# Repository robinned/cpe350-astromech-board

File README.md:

# cpe350-astromech-board
Main control board design for Cal Poly Robotics' astromech, Pascal. Designed by CPE350 Naboo Networks team.

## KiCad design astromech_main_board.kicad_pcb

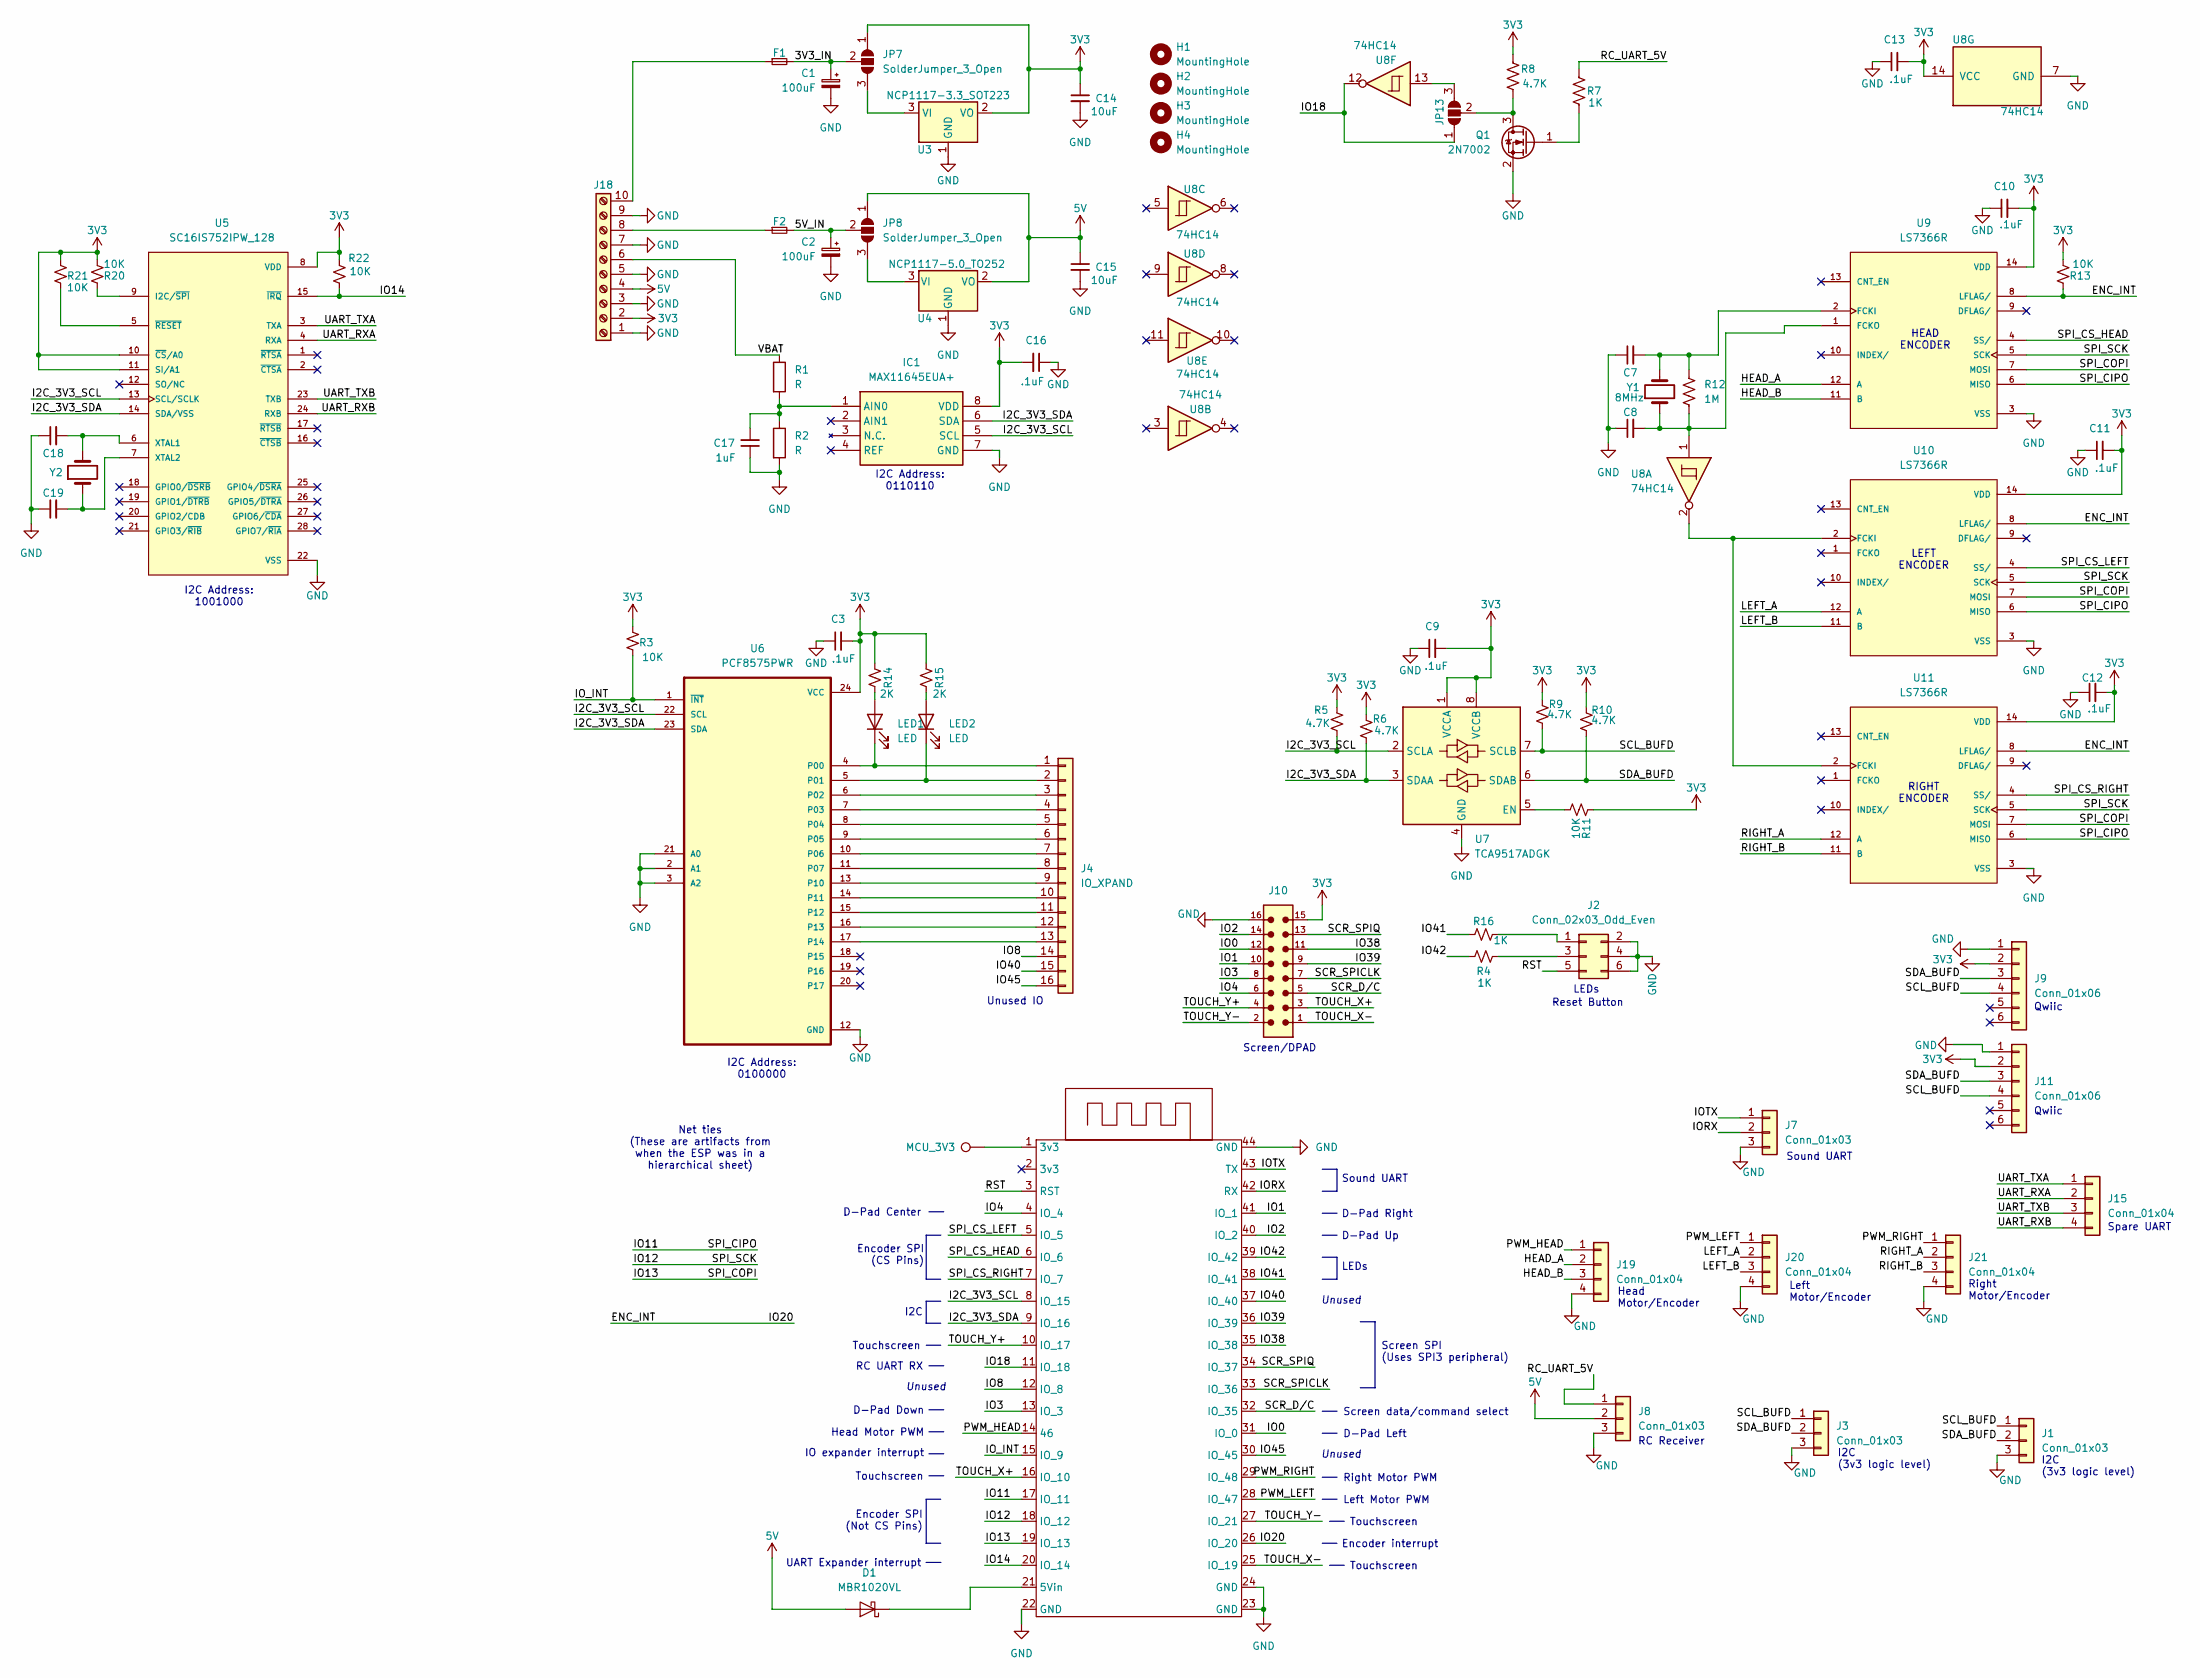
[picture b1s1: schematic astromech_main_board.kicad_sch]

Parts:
C1, C2: 100uF; CP_Elec_6.3x5.8
C3, C9, C10, C11, C12, C13, C16: .1uF; C_1206_3216Metric
C7, C8, C18, C19: C_Small; C_1206_3216Metric
C14, C15: 10uF; C_1206_3216Metric
C17: 1uF; C_1206_3216Metric
D1: MBR1020VL; D_SOD-123F
F1, F2: ??A; Fuseholder_Blade_Mini_Keystone_3568
H1, H2, H3, H4: MountingHole; MountingHole_3.2mm_M3
IC1: MAX11645EUA+; 21-0036K_MXM; Mouser Part Number 700-MAX11645EUA+
J1, J3, J7: Conn_01x03; 691210910003
J2: Conn_02x03_Odd_Even; PinHeader_2x03_P2.54mm_Vertical
J4: IO_XPAND; CUI_TBL009V-254-16GY-2GY
J8: Conn_01x03; PinSocket_1x03_P2.54mm_Vertical
J9, J11: Conn_01x06; CONN_SM04B-SRSS-TB_JST
J10: 61201621621; PART-NUMBER 61201621621
J15, J19, J20, J21: Conn_01x04; 691210910004
J18: Screw_Terminal_01x10; PHOENIX_1984691
JP7, JP8, JP13: SolderJumper_3_Open; SolderJumper-3_P1.3mm_Open_RoundedPad1.0x1.5mm
LED1, LED2: LED; LED_1206_3216Metric_Pad1.42x1.75mm_HandSolder
MCU_3V3: TestPoint; TestPoint_Pad_D1.0mm
Q1: 2N7002; SOT-23
R1, R2: R; R_1206_3216Metric
R3, R11, R13, R20, R21, R22: 10K; R_1206_3216Metric
R4, R7, R16: 1K; R_1206_3216Metric
R5, R6, R8, R9, R10: 4.7K; R_1206_3216Metric
R12: 1M; R_1206_3216Metric
R14, R15: 2K; R_1206_3216Metric
U3: NCP1117-3.3_SOT223; SOT-223-3_TabPin2
U4: NCP1117-5.0_TO252; TO-252-2
U5: SC16IS752IPW_128; SOP65P640X110-28N; PARTREV 9
U6: PCF8575PWR; SOP65P640X120-24N
U7: TCA9517ADGK; VSSOP-8_3x3mm_P0.65mm
U8: 74HC14; SOIC127P600X175-14N
U9, U10, U11: LS7366R; SOIC14_LS7366R_LSI; PARTREV June 2014
U13: YD-ESP32-S3
Y1: 8MHz; Crystal_SMD_Abracon_ABM3-2Pin_5.0x3.2mm
Y2: Crystal; Crystal_HC49-U_Vertical

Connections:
3V3: C3.2, C9.2, C10.2, C11.2, C12.2, C13.2, C14.1, C16.2, IC1.8 (VDD), J9.2, J10.15, J11.2, J18.2, JP7.1 (A), R3.1, R5.1, R6.1, R8.1, R9.1, R10.1, R11.1, R13.1, R14.1, R15.1, R20.1, R21.1, R22.2, U3.2 (VO), U5.8 (VDD), U5.10 (~CS/A0), U5.11 (SI/A1), U6.24 (VCC), U7.1 (VCCA), U7.8 (VCCB), U8.14 (VCC), U9.14 (VDD), U10.14 (VDD), U11.14 (VDD)
5V: C15.1, D1.2 (A), J8.2, J18.4, JP8.1 (A), U4.2 (VO)
/3V3_IN: C1.1, F1.2, JP7.2 (C)
/5V_IN: C2.1, F2.2, JP8.2 (C)
/ENC_INT: R13.2, U9.8 (LFLAG/), U10.8 (LFLAG/), U11.8 (LFLAG/), U13.26 (IO_20)
/HEAD_A: J19.2, U9.12 (A)
/HEAD_B: J19.3, U9.11 (B)
/I2C_3V3_SCL: IC1.5 (SCL), R5.2, U5.13 (SCL/SCLK), U6.22 (SCL), U7.2 (SCLA), U13.8 (IO_15)
/I2C_3V3_SDA: IC1.6 (SDA), R6.2, U5.14 (SDA/VSS), U6.23 (SDA), U7.3 (SDAA), U13.9 (IO_16)
/IO0: J10.12, U13.31 (IO_0)
/IO1: J10.10, U13.41 (IO_1)
/IO2: J10.14, U13.40 (IO_2)
/IO3: J10.8, U13.13 (IO_3)
/IO4: J10.6, U13.4 (IO_4)
/IO8: J4.14, U13.12 (IO_8)
/IO11: U9.6 (MISO), U10.6 (MISO), U11.6 (MISO), U13.17 (IO_11)
/IO12: U9.5 (SCK), U10.5 (SCK), U11.5 (SCK), U13.18 (IO_12)
/IO13: U9.7 (MOSI), U10.7 (MOSI), U11.7 (MOSI), U13.19 (IO_13)
/IO14: R22.1, U5.15 (~IRQ), U13.20 (IO_14)
/IO18: JP13.1 (A), U8.12, U13.11 (IO_18)
/IO38: J10.11, U13.35 (IO_38)
/IO39: J10.9, U13.36 (IO_39)
/IO40: J4.15, U13.37 (IO_40)
/IO41: R16.1, U13.38 (IO_41)
/IO42: R4.1, U13.39 (IO_42)
/IO45: J4.16, U13.30 (IO_45)
/IORX: J7.2, U13.42 (RX)
/IOTX: J7.1, U13.43 (TX)
/IO_INT: R3.2, U6.1 (~INT), U13.15 (IO_9)
/LEFT_A: J20.2, U10.12 (A)
/LEFT_B: J20.3, U10.11 (B)
/PWM_HEAD: J19.1, U13.14 (46)
/PWM_LEFT: J20.1, U13.28 (IO_47)
/PWM_RIGHT: J21.1, U13.29 (IO_48)
/RC_UART_5V: J8.1, R7.1
/RIGHT_A: J21.2, U11.12 (A)
/RIGHT_B: J21.3, U11.11 (B)
/RST: J2.5, U13.3 (RST)
/SCL_BUFD: J1.1, J3.1, J9.4, J11.4, R9.2, U7.7 (SCLB)
/SCR_D/C: J10.5, U13.32 (IO_35)
/SCR_SPICLK: J10.7, U13.33 (IO_36)
/SCR_SPIQ: J10.13, U13.34 (IO_37)
/SDA_BUFD: J1.2, J3.2, J9.3, J11.3, R10.2, U7.6 (SDAB)
/SPI_CS_HEAD: U9.4 (SS/), U13.6 (IO_6)
/SPI_CS_LEFT: U10.4 (SS/), U13.5 (IO_5)
/SPI_CS_RIGHT: U11.4 (SS/), U13.7 (IO_7)
/TOUCH_X+: J10.3, U13.16 (IO_10)
/TOUCH_X-: J10.1, U13.25 (IO_19)
/TOUCH_Y+: J10.4, U13.10 (IO_17)
/TOUCH_Y-: J10.2, U13.27 (IO_21)
/UART_RXA: J15.2, U5.4 (RXA)
/UART_RXB: J15.4, U5.24 (RXB)
/UART_TXA: J15.1, U5.3 (TXA)
/UART_TXB: J15.3, U5.23 (TXB)
/VBAT: J18.6, R1.1
GND: C1.2, C2.2, C3.1, C7.1, C8.1, C9.1, C10.1, C11.1, C12.1, C13.1, C14.2, C15.2, C16.1, C17.1, C18.1, C19.1, IC1.7 (GND), J1.3, J2.2, J2.4, J2.6, J3.3, J7.3, J8.3, J9.1, J10.16, J11.1, J18.1, J18.3, J18.5, J18.7, J18.9, J19.4, J20.4, J21.4, Q1.2 (S), R2.2, U3.1 (GND), U4.1 (GND), U5.22 (VSS), U6.2 (A1), U6.3 (A2), U6.12 (GND), U6.21 (A0), U7.4 (GND), U8.7 (GND), U9.3 (VSS), U10.3 (VSS), U11.3 (VSS), U13.22 (GND), U13.23 (GND), U13.24 (GND), U13.44 (GND)
unnamed: D1.1 (K), U13.21 (5Vin)
unnamed: C17.2, IC1.1 (AIN0), R1.2, R2.1
unnamed: J2.1, R16.2
unnamed: J2.3, R4.2
unnamed: J4.1, LED1.1 (K), U6.4 (P00)
unnamed: J4.2, LED2.1 (K), U6.5 (P01)
unnamed: J4.3, U6.6 (P02)
unnamed: J4.4, U6.7 (P03)
unnamed: J4.5, U6.8 (P04)
unnamed: J4.6, U6.9 (P05)
unnamed: J4.7, U6.10 (P06)
unnamed: J4.8, U6.11 (P07)
unnamed: J4.9, U6.13 (P10)
unnamed: J4.10, U6.14 (P11)
unnamed: J4.11, U6.15 (P12)
unnamed: J4.12, U6.16 (P13)
unnamed: J4.13, U6.17 (P14)
unnamed: F2.1, J18.8
unnamed: F1.1, J18.10
unnamed: JP7.3 (B), U3.3 (VI)
unnamed: JP8.3 (B), U4.3 (VI)
unnamed: JP13.3 (B), U8.13
unnamed: JP13.2 (C), Q1.3 (D), R8.2
unnamed: LED1.2 (A), R14.2
unnamed: LED2.2 (A), R15.2
unnamed: MCU_3V3.1, U13.1 (3v3)
unnamed: Q1.1 (G), R7.2
unnamed: R20.2, U5.9 (I2C/~SPI)
unnamed: C18.2, U5.6 (XTAL1), Y2.2
unnamed: C19.2, U5.7 (XTAL2), Y2.1
unnamed: R21.2, U5.5 (~RESET)
unnamed: R11.2, U7.5 (EN)
unnamed: C7.2, R12.1, U9.2 (FCKI), Y1.2
unnamed: C8.2, R12.2, U8.1, U9.1 (FCKO), Y1.1
unnamed: U8.2, U10.2 (FCKI), U11.2 (FCKI)

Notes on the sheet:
Head Motor PWM
D-Pad Right
Reset Button
Net ties (These are artifacts from when the ESP was in a hierarchical sheet)
D-Pad Left
Screen SPI (Uses SPI3 peripheral)
I2C
Qwiic
RC UART RX
UART Expander interrupt
Right Motor/Encoder
Touchscreen
Unused IO
Encoder SPI (Not CS Pins)
Encoder interrupt
Encoder SPI (CS Pins)
RIGHT ENCODER
Right Motor PWM
I2C (3v3 logic level)
LEDs
IO expander interrupt
I2C Address: 0110110
Sound UART
LEFT ENCODER
D-Pad Center
Unused
D-Pad Down
HEAD ENCODER
Left Motor PWM
Screen/DPAD
Spare UART
Screen data/command select
Head Motor/Encoder
D-Pad Up
Left Motor/Encoder
I2C Address: 1001000
I2C Address: 0100000
RC Receiver

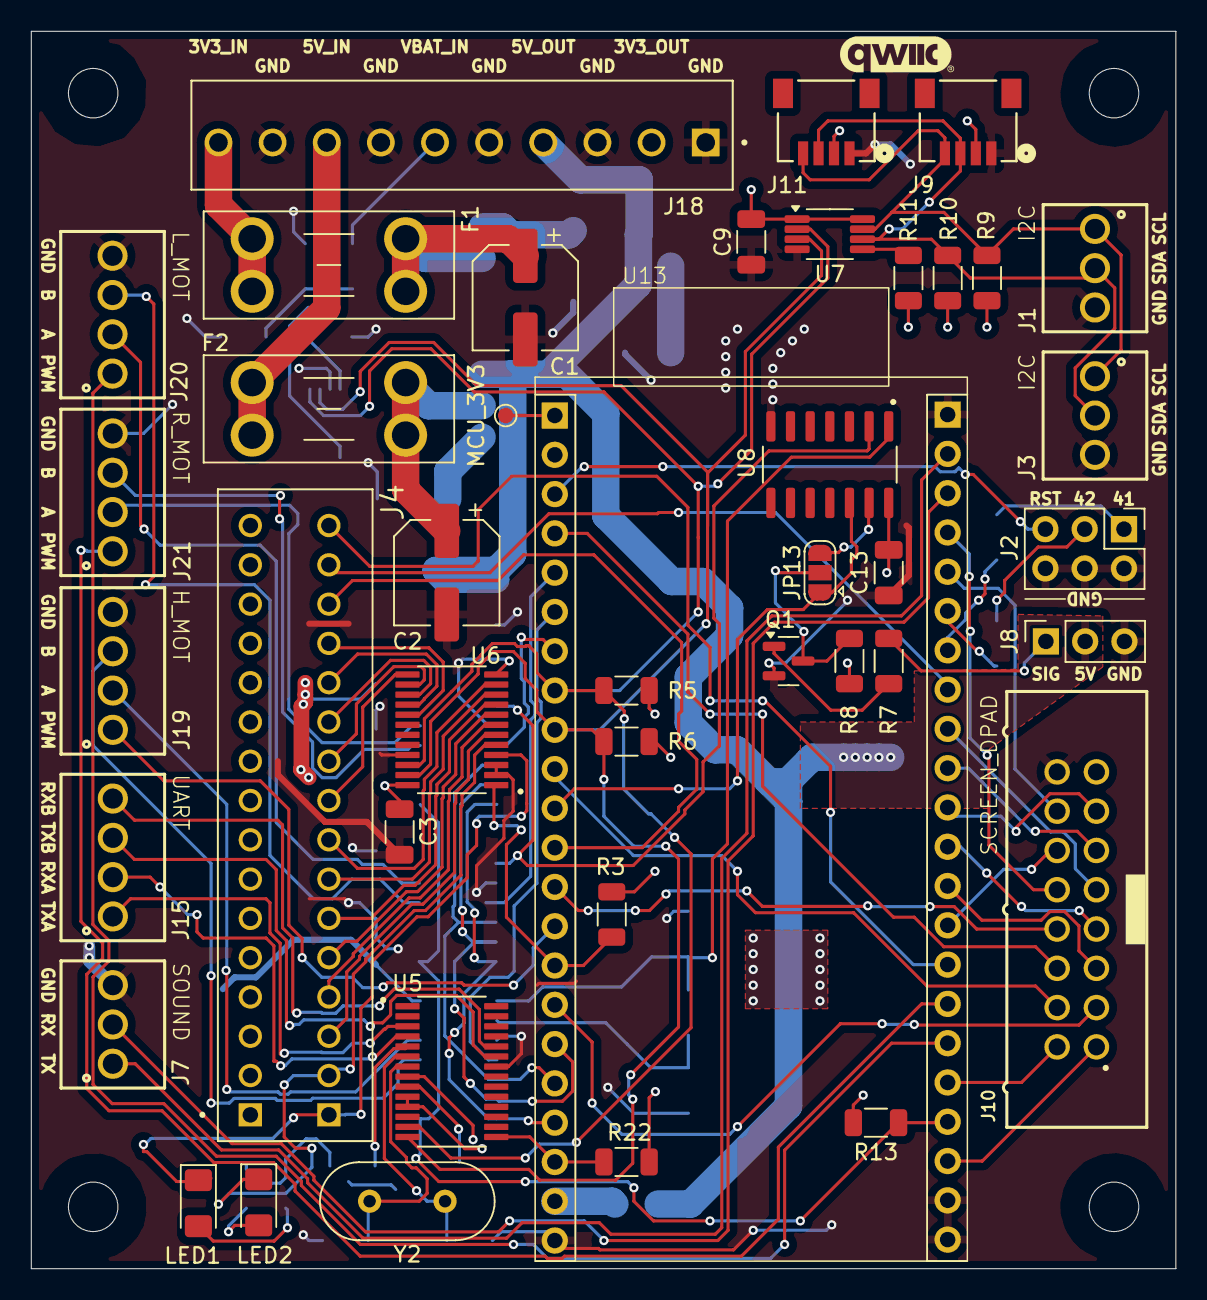
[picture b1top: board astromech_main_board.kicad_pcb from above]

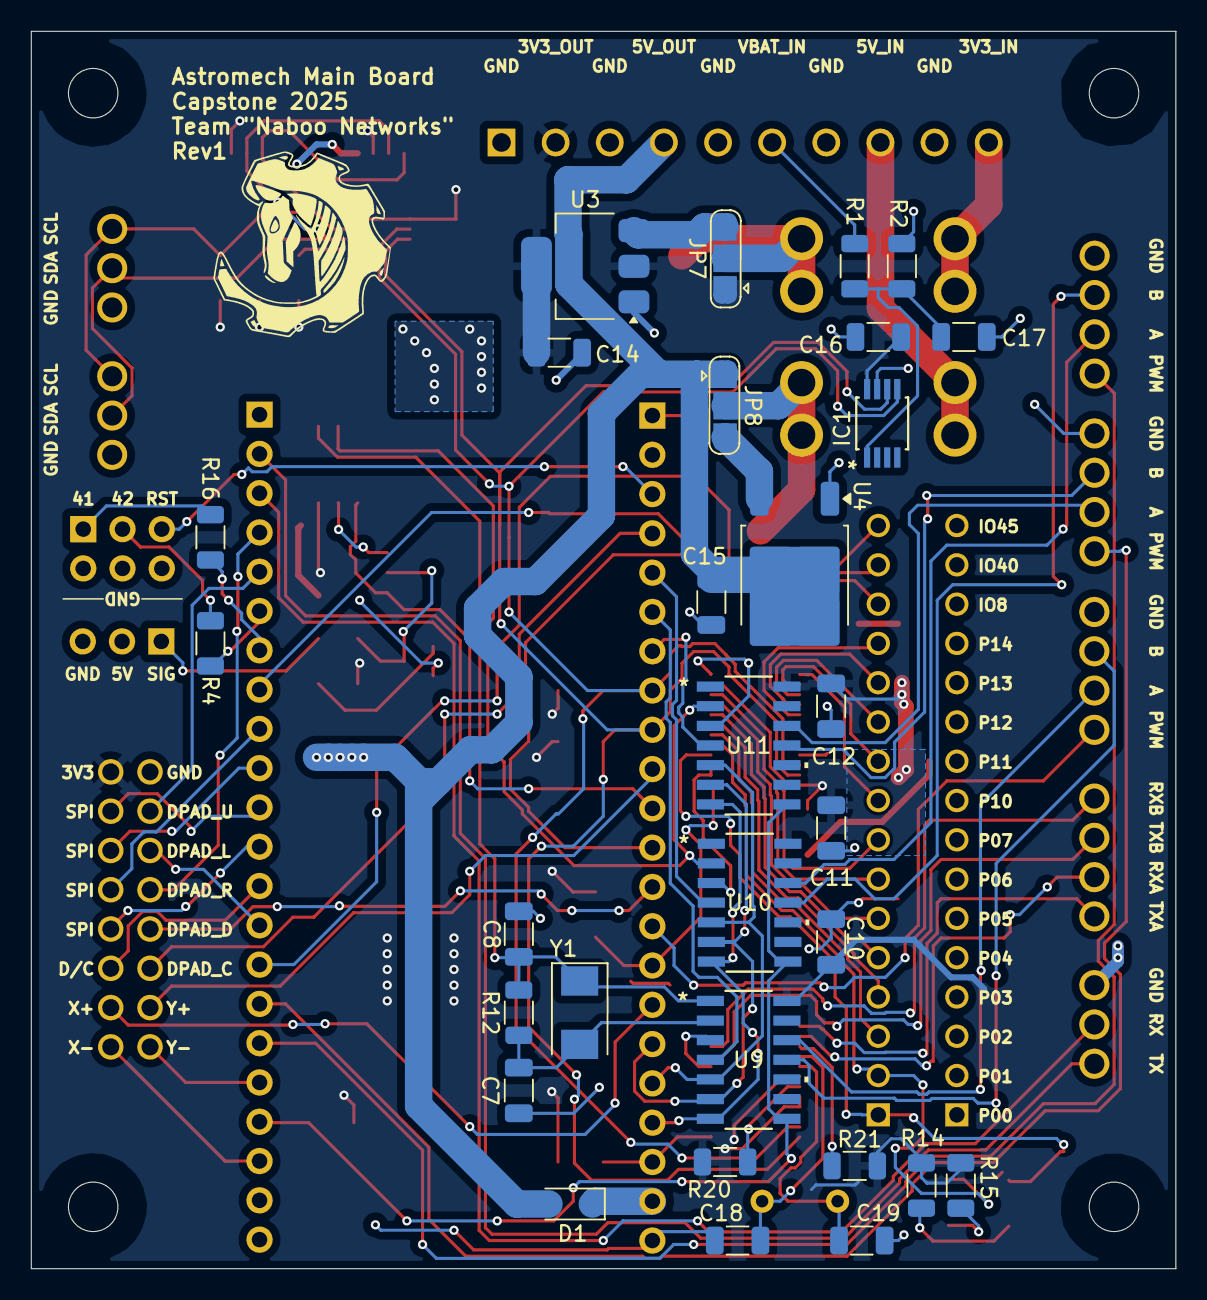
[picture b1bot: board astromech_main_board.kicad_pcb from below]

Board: 2 copper layers, 74.0 x 80.0 mm, 76 parts (30 on the bottom side), 91 nets.

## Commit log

2024-10-04 project initialized
2024-10-17 added ESP board
2024-10-28 added blocks
2024-10-28 added yd-esp32-s3
2024-10-28 wire GND
    Added some wires and GND
2024-10-28 first try
2024-10-28 added labels to io_prot
2024-11-08 Updated Power Protection
    Added:
    - Solder Jumper
    - Two Input Voltages 3.3 and 5.0
    - Voltage Regulators
2024-11-10 voltage monitoring schematic done
2024-11-10 added i2c to io_protection
2024-11-10 added i2c buffer + wired a0 to gnd
2024-11-10 added all block interface pins
2024-11-13 Updated IO Expander
    Created bus input (SCL, SDA, INT) and bus output (PO{15:0}).
    Using the TCA9554 Low Voltage 8-Bit for I2C communication. The output of PO is tied to the VCC input and each address is configurable with solder jumpers being tied to either VCC or GND.
2024-11-13 added hw encoder
2024-11-14 ESP32 mostly done
2024-12-20 moved power protection
2024-12-20 moved voltage monitoring
2024-12-20 moved io expander
2024-12-29 moved encoder
2025-01-09 Updated MCU
2025-01-17 consolidated schematic
2025-01-21 add qwiic connectors
2025-01-22 added missing files
2025-01-23 Connections 98%
    - Pushing Before Deleting Connection
    - Was able to connect all the labels except for ENC_INT for IO20. When highlighting connections, it is not showing up. :(
2025-01-23 Connections deleted, ENC_INT works
    - Pushing before deleting MCU and fitting ESP to sheet
    - Deleted all the connections for root
    - ENC_INT now highlights for some reason??
2025-01-23 Resized Sheet in root
    - Will delete MCU tomorrow...
    - Check in with Eva
2025-01-24 Removed Block
    - Everything should be on page
2025-01-31 some board done
2025-02-01 added 8mil trace/space constraints to board
2025-02-03 added UART chip
2025-02-03 started routing
2025-02-03 made encoders 3v3
2025-02-04 layout mostly done
2025-02-04 main routing done
2025-02-04 3v3 routed
2025-02-04 changed board setup to 8mil trace/spacing
2025-02-04 renamed directory
2025-02-04 renamed nets
2025-02-06 compact layout start
2025-02-07 implemented suggestions
2025-02-07 added values, 2N7002, and updated unused pins
2025-02-07 switch qwiic pinout order
2025-02-08 schematic updates
2025-02-08 new layout
2025-02-08 new layout done
2025-02-09 somewhat routed
2025-02-09 finished routing
2025-02-09 switched motor terminal positions, adjusted silkscreen and routing
2025-02-09 reordered terminal blocks
2025-02-11 added silkscreen
2025-02-11 fixed pinout and some silkscreen labels
2025-02-11 added keepout near mounting holes
2025-02-11 added diode
2025-02-11 updated part values
2025-02-15 added version 1.0 of board
